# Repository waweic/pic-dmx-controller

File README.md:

# pic-dmx-controller
A friend of mine did in his Internship at the Institute for Automation some developing.
He used the CCS C-Compiler, so You will have to use the same.
In the main Folder, you will find a .hex and a .dll file. The .hex file should be flashed to a PIC18f4550, the .dll file is a plugin for PCDIMMER. The Electronics are not yet tested on a real DMX-Device, but they ARE tested on a Oscillsocope. 
The electronics should cost about 15€, but you don't have to use the most expensive parts, e.d the DC/DC Converter and the Octocoupler.
To use the Plugin, You first have to install the Driver, brought in the Driver Folder. 
It is until now just made for Windows and i would really like, if somebody could implement a linux driver.

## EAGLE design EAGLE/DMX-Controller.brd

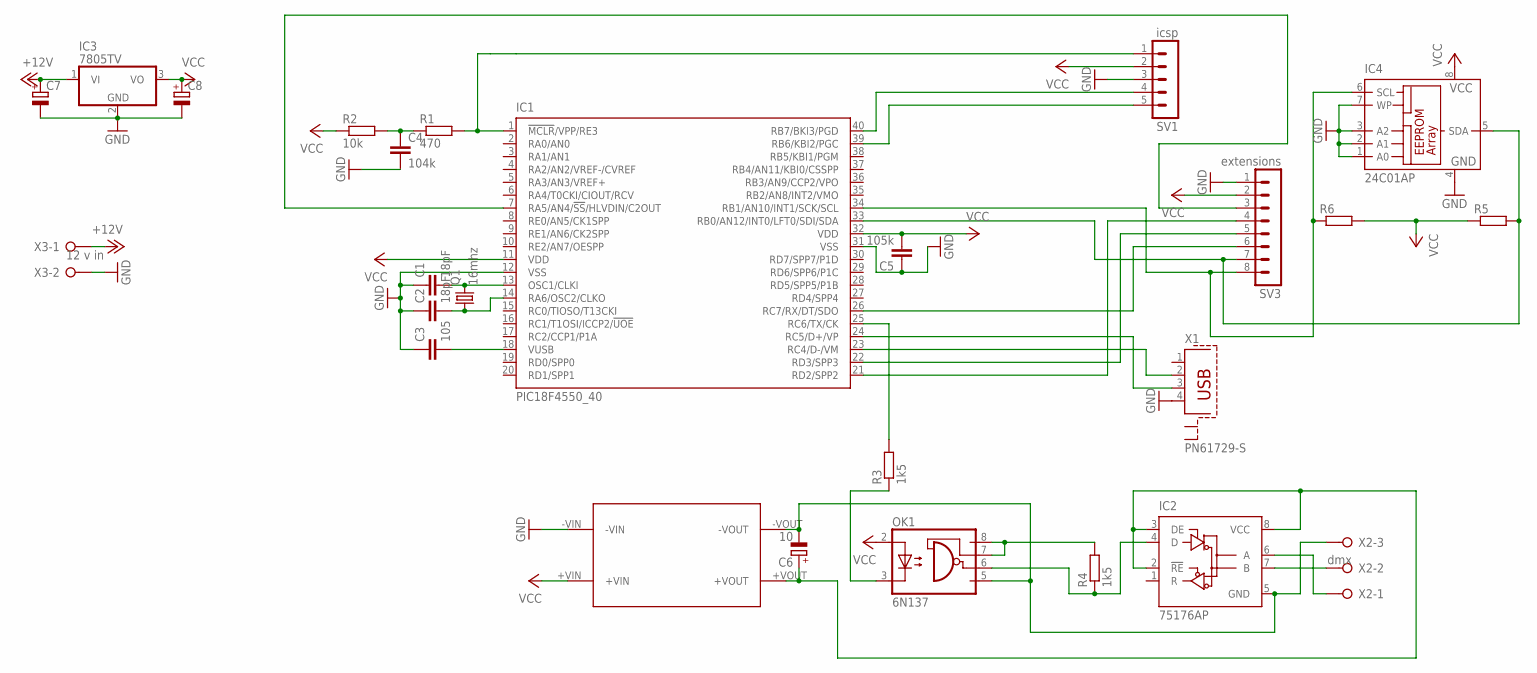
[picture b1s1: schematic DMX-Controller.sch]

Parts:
C1, C2: 18pF; C050-024X044
C3: 105; C050-024X044
C4: 104k; C050-024X044
C5: 105k; C050-024X044
C6: 10; E2,5-6
C7, C8: CPOL-EUE2.5-6; E2,5-6
IC1: PIC18F4550_40; DIL40
IC2: 75176AP; DIL08
IC3: 7805TV; TO220V
IC4: 24C01AP; DIL8
OK1: 6N137; DIL08
Q1: 16mhz; HC49U-V
R1: 470; 0207/10
R2: 10k; 0207/10
R3, R4: 1k5; 0207/10
R5, R6: R-EU_0207/10; 0207/10
SV1: icsp; MA05-1
SV3: extensions; MA08-1
U$1: SIM1-0505SZ; SIM-0505SZ
X1: PN61729-S
X2: dmx; W237-3E
X3: 12 v in; W237-132

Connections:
+12V: C7.+, IC3.1 (VI), X3.1
GND: C1.1, C2.1, C3.1, C4.2, C5.1, C7.-, C8.-, IC1.12 (VSS), IC1.31 (VSS), IC3.2 (GND), IC4.1 (A0), IC4.2 (A1), IC4.3 (A2), IC4.4 (GND), IC4.7 (WP), SV1.3, SV3.1, U$1.-VIN, X1.4, X3.2
unnamed: C1.2, IC1.13 (OSC1/CLKI), Q1.2
unnamed: C2.2, IC1.14 (RA6/OSC2/CLKO), Q1.1
unnamed: C3.2, IC1.18 (VUSB)
unnamed: IC1.1 (!MCLR!/VPP/RE3), R1.2, SV1.1
unnamed: IC1.7 (RA5/AN4/!SS!/HLVDIN/C2OUT), SV3.3
unnamed: IC1.40 (RB7/BKI3/PGD), SV1.4
unnamed: IC1.24 (RC5/D+/VP), X1.3
unnamed: IC1.23 (RC4/D-/VM), X1.2
unnamed: IC1.39 (RB6/KBI2/PGC), SV1.5
unnamed: OK1.3 (C), R3.1
unnamed: C6.-, IC2.5 (GND), OK1.5 (GND), U$1.-VOUT, X2.3
unnamed: C6.+, IC2.2 (!RE), IC2.3 (DE), IC2.8 (VCC), U$1.+VOUT
unnamed: IC1.25 (RC6/TX/CK), R3.2
unnamed: IC1.34 (RB1/AN10/INT1/SCK/SCL), IC4.6 (SCL), R6.1, SV3.8
unnamed: IC1.21 (RD2/SPP2), SV3.4
unnamed: OK1.7 (VE), OK1.8 (VCC), R4.2
unnamed: IC2.4 (D), OK1.6 (VO), R4.1
unnamed: IC1.22 (RD3/SPP3), SV3.5
unnamed: IC1.26 (RC7/RX/DT/SDO), SV3.6
unnamed: IC1.33 (RB0/AN12/INT0/LFT0/SDI/SDA), IC4.5 (SDA), R5.2, SV3.7
unnamed: IC2.6 (A), X2.1
unnamed: IC2.7 (B), X2.2
unnamed: C4.1, R1.1, R2.2
VCC: C5.2, C8.+, IC1.11 (VDD), IC1.32 (VDD), IC3.3 (VO), IC4.8 (VCC), OK1.2 (A), R2.1, R5.1, R6.2, SV1.2, SV3.2, U$1.+VIN

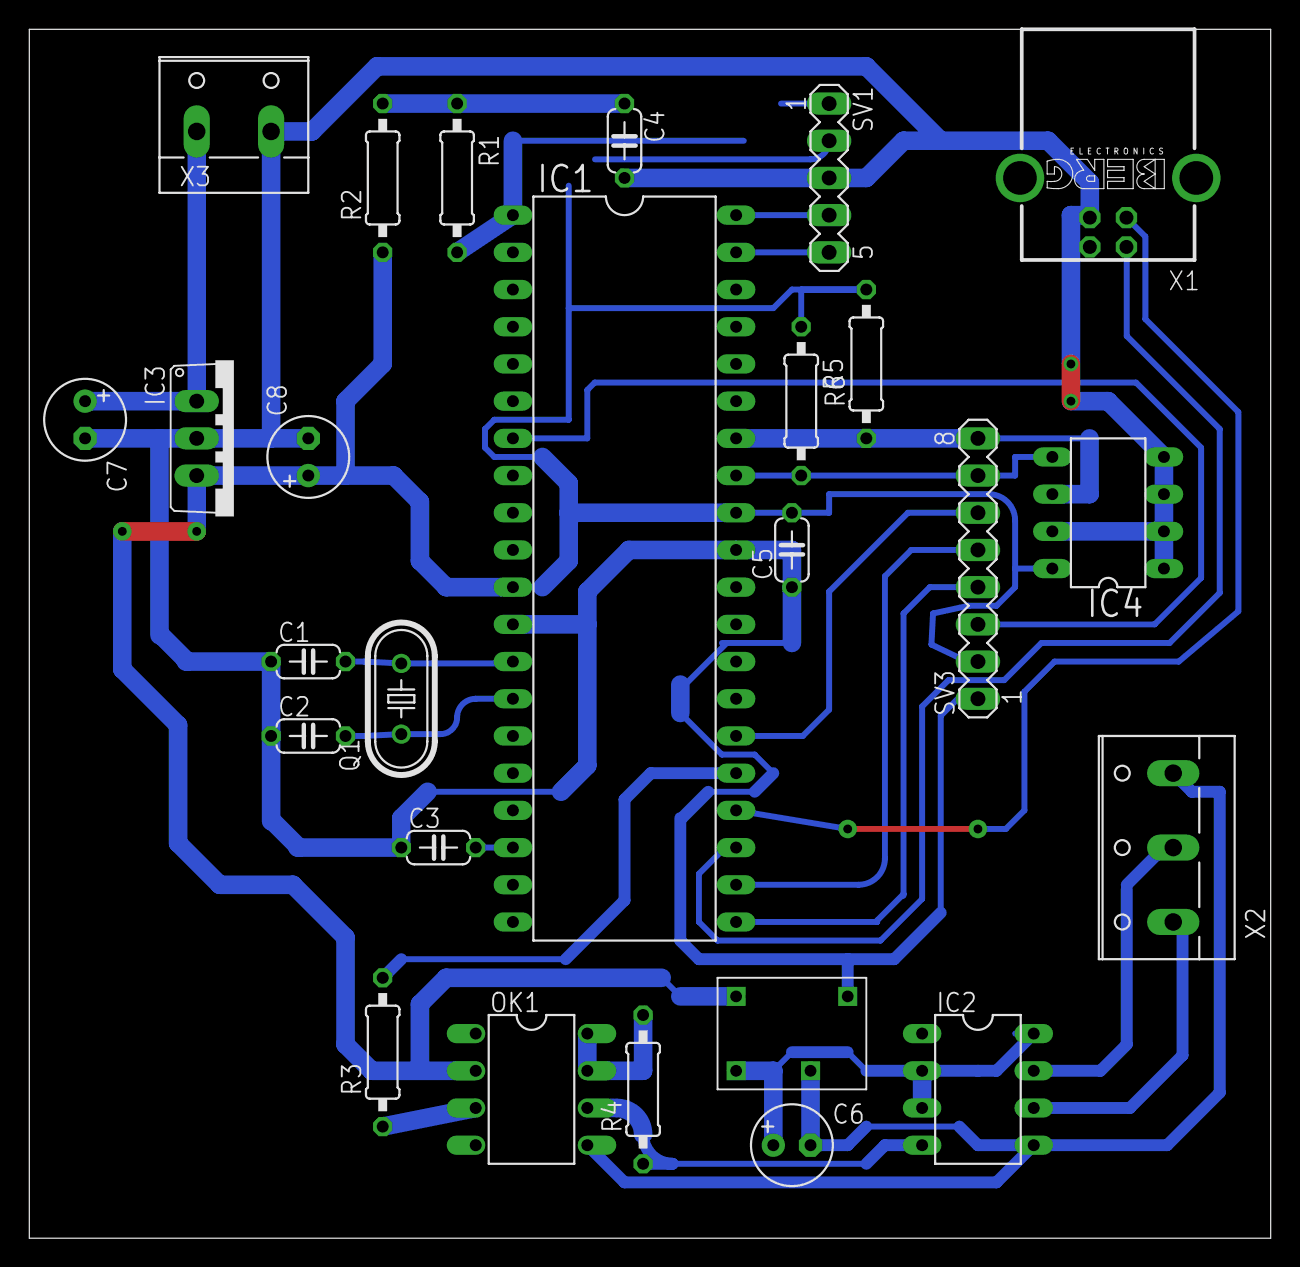
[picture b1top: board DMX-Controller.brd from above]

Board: 2 copper layers, 84.8 x 82.5 mm, 26 parts (0 on the bottom side), 26 nets.

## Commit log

2017-07-25 Update README.md
    Added some Changes
2018-09-15 Update main.c
    Added comments
